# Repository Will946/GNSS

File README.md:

# ZED-F9P RTK GPS Receiver

Board for an autonomous cart that follows the edge of a lawn and sprays weed killer along the border. Goal is centimeter level positioning using RTK corrections so the cart can hold a precise line along a mapped boundary. Prototyping this board is the only part of the project built so far.

## Status

Not currently in use on the cart. Prototyping this board cost way more than expected, and the rest of the cart, drive base, sprayer, controller, was never built as a result. Right now this is just the GNSS board sitting on its own.

## Overview

The ZED-F9P decodes both L1 and L2 bands at the same time, which speeds up how fast it locks a fixed RTK solution and helps under partial sky obstruction, useful near fences, trees, or the edge of a house. With a clear view of sky and a valid RTCM3 correction stream, this board is capable of about 10 mm 3D accuracy.

Two things it needs to actually hit that accuracy:
- Clear sky view. RTK does not work well indoors or under heavy tree cover.
- A correction stream, either from a second ZED-F9P set up as a base station, or from an NTRIP correction service.

## Features

- u-blox ZED-F9P module, L1/L2 dual band, multi constellation
- Rover mode for the cart, with base station mode available if running your own fixed reference
- About 10 mm 3D accuracy with valid RTK corrections
- Update rates up to 20 Hz in high precision RTK mode
- Five simultaneous communication interfaces, see below
- U.FL antenna connector for a low profile L1/L2 active antenna
- Rechargeable backup cell that keeps module config and almanac data through power off, so warm starts are faster. Holds state for roughly two weeks unpowered
- Status LEDs for power, PPS, and fix state

## Communication Interfaces

| Interface | Description |
|---|---|
| USB-C | Enumerates as a standard COM port, carries power and full UBX/NMEA data |
| UART1 | 3.3V TTL, general purpose NMEA/UBX I/O |
| UART2 | 3.3V TTL, dedicated to RTCM3 correction data. Input on a rover, output on a base |
| I2C DDC | u-blox's I2C implementation, shares physical pins with SPI |
| SPI | Alternate to I2C on the same pins, must be explicitly selected |

Interface select jumper: I2C and SPI share pins, so only one is active at a time.
- Jumper open, default: I2C/DDC enabled, UART1 and I2C both active
- Jumper closed: SPI enabled, this disables UART1 and I2C

Set this before wiring your host MCU. An unexpected jumper state is the most common reason I2C or SPI fails to come up.

## Hardware

| Item | Detail |
|---|---|
| GNSS module | u-blox ZED-F9P |
| Antenna connector | U.FL, active antenna with bias tee power |
| Antenna requirement | L1/L2 dual band active GNSS antenna |
| Logic level | 3.3V |
| Backup power | Rechargeable cell, retains config/almanac about 2 weeks unpowered |
| Board interconnect | 0.1" breadboard compatible headers |
| Input power | 5V or 3.3V |

## Pinout

| Pin | Function | Notes |
|---|---|---|
| 5V / 3V3 | Power in | Select per your supply |
| GND | Ground | |
| TX1 / RX1 | UART1, NMEA/UBX | 3.3V TTL, general data |
| TX2 / RX2 | UART2, RTCM3 | 3.3V TTL, correction data in/out |
| SDA / SCL | I2C, DDC | Shares pins with SPI, see jumper |
| MISO / MOSI / SCK / CS | SPI | Enabled only when jumper closed |
| PPS | Pulse per second | Precision timing output |
| SAFEBOOT | Firmware recovery | Pull low during boot to enter recovery |

## Getting Started

1. Connect an active L1/L2 GNSS antenna to the U.FL connector.
2. Set the I2C/SPI select jumper to match your intended interface. Default is open, I2C.
3. Power the board from 5V or 3.3V.
4. Connect to the module with a UBX capable configuration tool such as u-center over USB or UART1 to check satellite lock and fix status.
5. Once a valid 3D fix shows up, move to RTK setup below.

## RTK Setup

As a rover on the cart:
- Feed RTCM3 correction messages into UART2, or via I2C/SPI if you'd rather.
- Once corrections are flowing and satellite geometry cooperates, fix state moves from no fix to 3D to RTK float to RTK fixed.
- Fixed RTK is what you want before trusting the position for holding a line along the lawn edge.

If running your own base station instead of NTRIP:
- Configure survey in mode with a target accuracy and minimum observation time, for example 60 seconds and 2 meters.
- Once survey in completes, the module holds a fixed reference position and starts outputting RTCM3 corrections on UART2.
- Typical RTCM3 messages to enable: 1005 for station coordinates, 1077, 1087, 1097, 1127 for per constellation observations, 1230 for GLONASS bias.

Correction delivery options:
- A radio telemetry link, LoRa or 900 MHz, between a yard mounted base and the cart
- An NTRIP client and caster over the internet for networked corrections

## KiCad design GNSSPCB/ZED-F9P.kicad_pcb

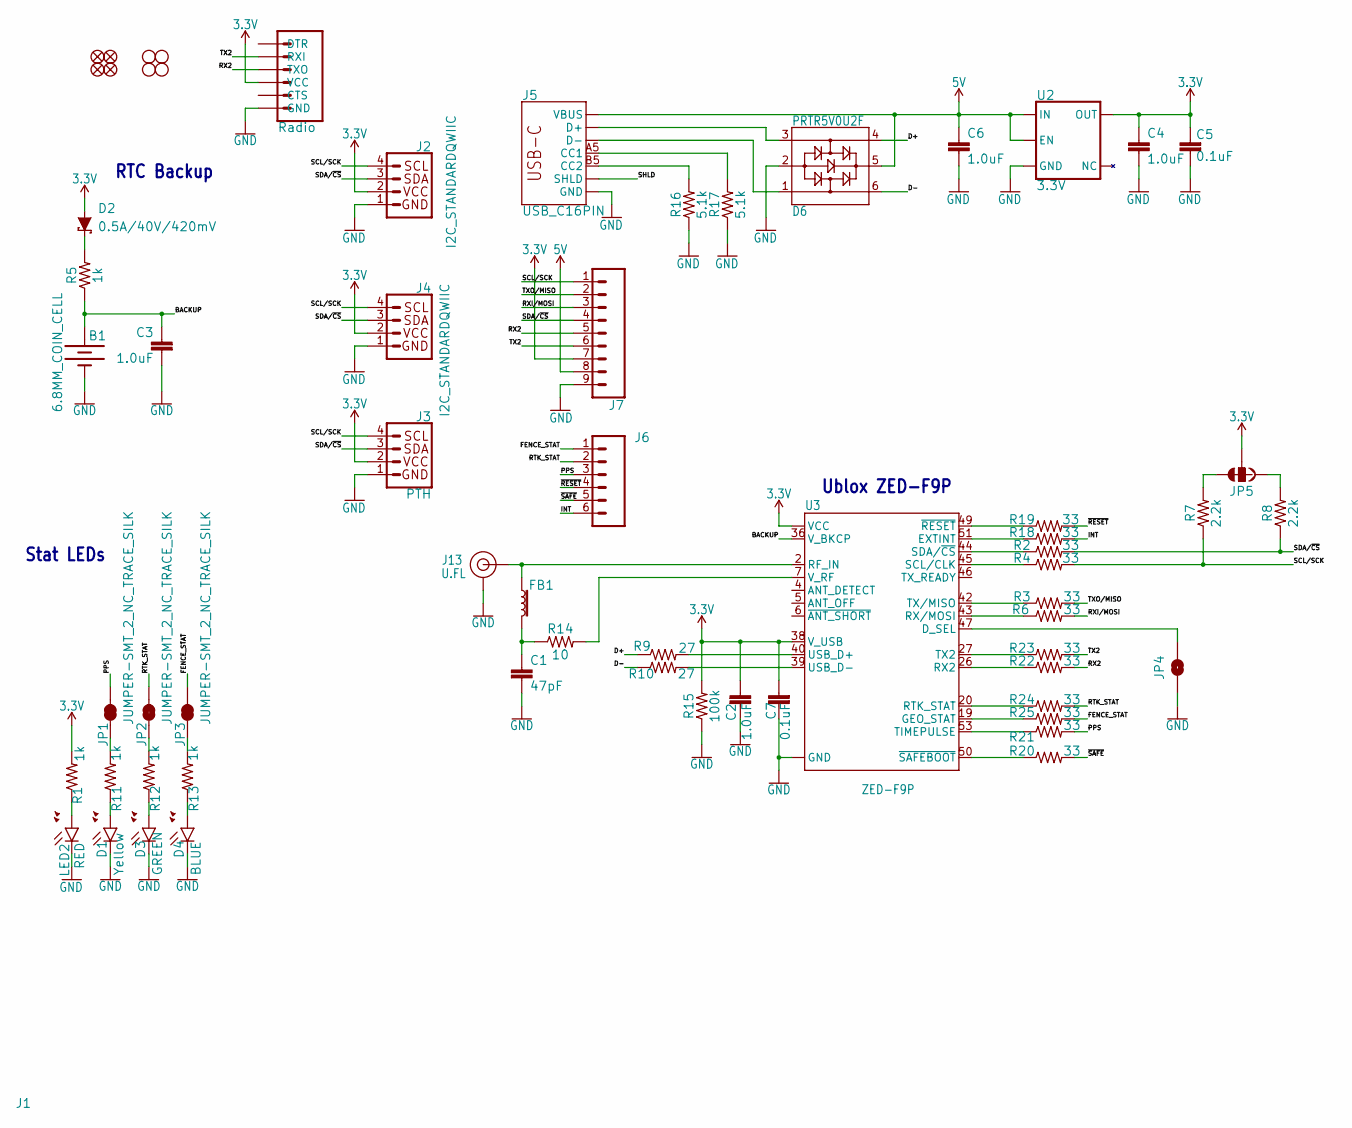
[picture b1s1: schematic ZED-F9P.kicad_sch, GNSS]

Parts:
B1: 6.8MM_COIN_CELL; BATTCON-6.8MM
C1: 47pF; 0603
C2, C3, C4, C6: 1.0uF; 0603
C5, C7: 0.1uF; 0603
D1: Yellow; LED-0603
D2: 0.5A/40V/420mV; SOD-323
D3: GREEN; LED-0603
D4: BLUE; LED-0603
D6: PRTR5V0U2F; SOT886
FB1: FERRITE_BEAD-120_OHM-0402; 0402
J1: Radio; 1X06_NO_SILK
J2, J4: I2C_STANDARDQWIIC; 1X04_1MM_RA
J3: PTH; 1X04_NO_SILK
J5: USB_C16PIN; USB-C-16P
J6: CONN_06NO_SILK_FEMALE_PTH; 1X06_NO_SILK
J7: CONN_09NO_SILK; 1X09_NO_SILK
J13: U.FL
JP1, JP2, JP3: JUMPER-SMT_2_NC_TRACE_SILK; SMT-JUMPER_2_NC_TRACE_SILK
JP4: JUMPER-SMT_2_NO_SILK; SMT-JUMPER_2_NO_SILK
JP5: JUMPER-SMT_3_2-NC_TRACE_SILK; SMT-JUMPER_3_2-NC_TRACE_SILK
JP21, JP61, JP71, JP81: FIDUCIALUFIDUCIAL; MICRO-FIDUCIAL
JP31, JP41, JP91, JP101: STAND-OFF
LED2: RED; LED-0603
R1, R5, R11, R12, R13: 1k; 0603
R2, R3, R4, R6, R18, R19, R20, R21, R22, R23, R24, R25: 33; 0603
R7, R8: 2.2k; 0603
R9, R10: 27; 0603
R14: 10; 0603
R15: 100k; 0603
R16, R17: 5.1k; 0603
U2: 3.3V; SOT23-5
U3: ZED-F9P

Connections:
3.3V: C2.1, C4.1, C5.2, C7.2, D2.A, J1.4 (VCC), J2.2, J3.2 (VCC), J4.2, J7.7, JP5.2, R1.2, R15.2, U2.5 (OUT), U3.33 (VCC), U3.34 (VCC), U3.38 (V_USB)
5V: C6.1, D6.5, J5.VBUS1 (VBUS), J5.VBUS2 (VBUS), J7.8, U2.1 (IN), U2.3 (EN)
ANT_VCC: C1.1, FB1.2, R14.1
BACKUP: B1.+, C3.1, R5.1, U3.36 (V_BKCP)
CC1: J5.A5 (CC1), R17.2
CC2: J5.B5 (CC2), R16.2
D+: D6.4, R9.1
D-: D6.6, R10.1
D_SEL: JP4.2, U3.47 (D_SEL)
FENCE_STAT: J6.1, JP3.2, R25.2
GND: B1.-, C1.2, C2.2, C3.2, C4.2, C5.1, C6.2, C7.1, D1.C, D3.C, D4.C, D6.2, J1.6 (GND), J2.1, J3.1 (GND), J4.1, J5.GND, J5.GND2 (GND), J7.9, J13.1 (GND), J13.2 (GND), JP4.1, LED2.C, R15.1, R16.1, R17.1, U2.2 (GND), U3.1 (GND), U3.3 (GND), U3.12 (GND), U3.14 (GND), U3.32 (GND), U3.37 (GND), U3.41 (GND), U3.48 (GND), U3.55 (GND), U3.56 (GND), U3.57 (GND), U3.58 (GND), U3.59 (GND), U3.60 (GND), U3.61 (GND), U3.62 (GND), U3.63 (GND), U3.64 (GND), U3.65 (GND), U3.66 (GND), U3.67 (GND), U3.68 (GND), U3.69 (GND), U3.70 (GND), U3.71 (GND), U3.72 (GND), U3.73 (GND), U3.74 (GND), U3.75 (GND), U3.76 (GND), U3.77 (GND), U3.78 (GND), U3.79 (GND), U3.80 (GND), U3.81 (GND), U3.82 (GND), U3.83 (GND), U3.84 (GND), U3.85 (GND), U3.86 (GND), U3.87 (GND), U3.88 (GND), U3.89 (GND), U3.90 (GND), U3.91 (GND), U3.92 (GND), U3.93 (GND), U3.94 (GND), U3.95 (GND), U3.96 (GND), U3.97 (GND), U3.98 (GND), U3.99 (GND), U3.100 (GND), U3.101 (GND), U3.102 (GND)
GPS_ANT1: FB1.1, J13.FEED (SIGNAL), U3.2 (RF_IN)
INT: J6.6, R18.2
unnamed: D3.A, R12.1
unnamed: D1.A, R11.1
unnamed: JP2.1, R12.2
unnamed: JP1.1, R11.2
unnamed: JP5.1, R8.2
unnamed: D2.C, R5.2
unnamed: D4.A, R13.1
unnamed: JP5.3, R7.2
unnamed: JP3.1, R13.2
unnamed: LED2.A, R1.1
unnamed: R9.2, U3.40 (USB_D+)
unnamed: R10.2, U3.39 (USB_D-)
unnamed: R14.2, U3.7 (V_RF)
unnamed: R22.1, U3.26 (RX2)
unnamed: R18.1, U3.51 (EXTINT)
unnamed: R19.1, U3.49 (~RESET)
unnamed: R21.1, U3.53 (TIMEPULSE)
unnamed: R20.1, U3.50 (~SAFEBOOT)
unnamed: R24.1, U3.20 (RTK_STAT)
unnamed: R25.1, U3.19 (GEO_STAT)
PPS: J6.3, JP1.2, R21.2
RTK_STAT: J6.2, JP2.2, R24.2
RX2: J1.3 (TXO), J7.5, R22.2
RXI/MOSI: J7.3, R6.2
RXLV: R6.1, U3.43 (RX/MOSI)
SCL/SCK: J2.4, J3.4 (SCL), J4.4, J7.1, R4.2, R7.1
SCL_LV: R4.1, U3.45 (SCL/CLK)
SDA/~CS: J2.3, J3.3 (SDA), J4.3, J7.4, R2.2, R8.1
SDA_LV: R2.1, U3.44 (SDA/~CS)
SHLD: J5.SHLD1 (SHLD), J5.SHLD2 (SHLD), J5.SHLD3 (SHLD), J5.SHLD4 (SHLD), J5.SHLD5 (SHLD), J5.SHLD6 (SHLD), J5.SHLD7 (SHLD), J5.SHLD8 (SHLD)
TX2: J1.2 (RXI), J7.6, R23.2
TX2_P: R23.1, U3.27 (TX2)
TXLV: R3.1, U3.42 (TX/MISO)
TXO/MISO: J7.2, R3.2
UNP_D+: D6.3, J5.A6 (D+), J5.B6 (D+)
UNP_D-: D6.1, J5.A7 (D-), J5.B7 (D-)
~RESET: J6.4, R19.2
~SAFE: J6.5, R20.2

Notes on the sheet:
RTC Backup
Stat LEDs
Ublox ZED-F9P

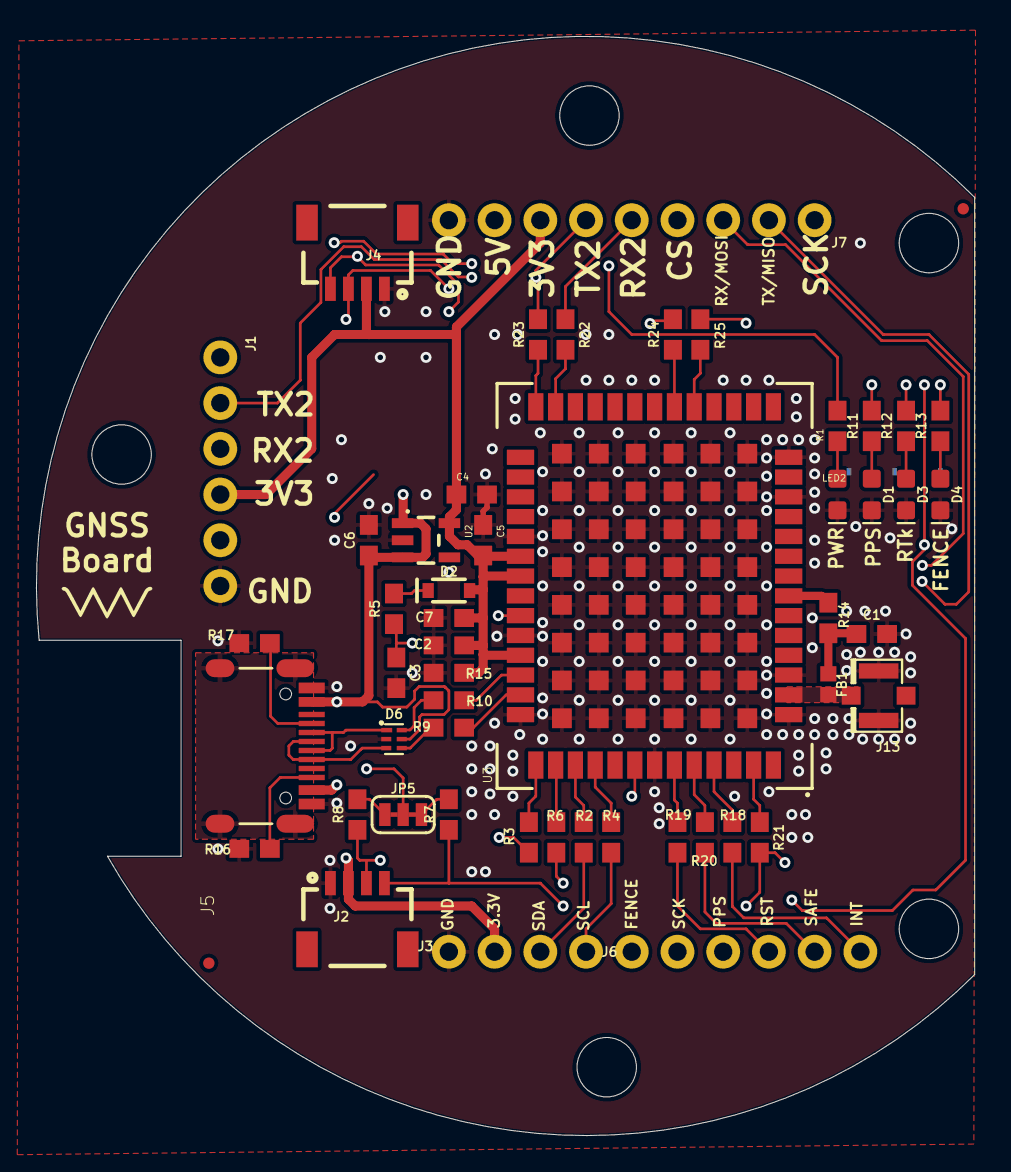
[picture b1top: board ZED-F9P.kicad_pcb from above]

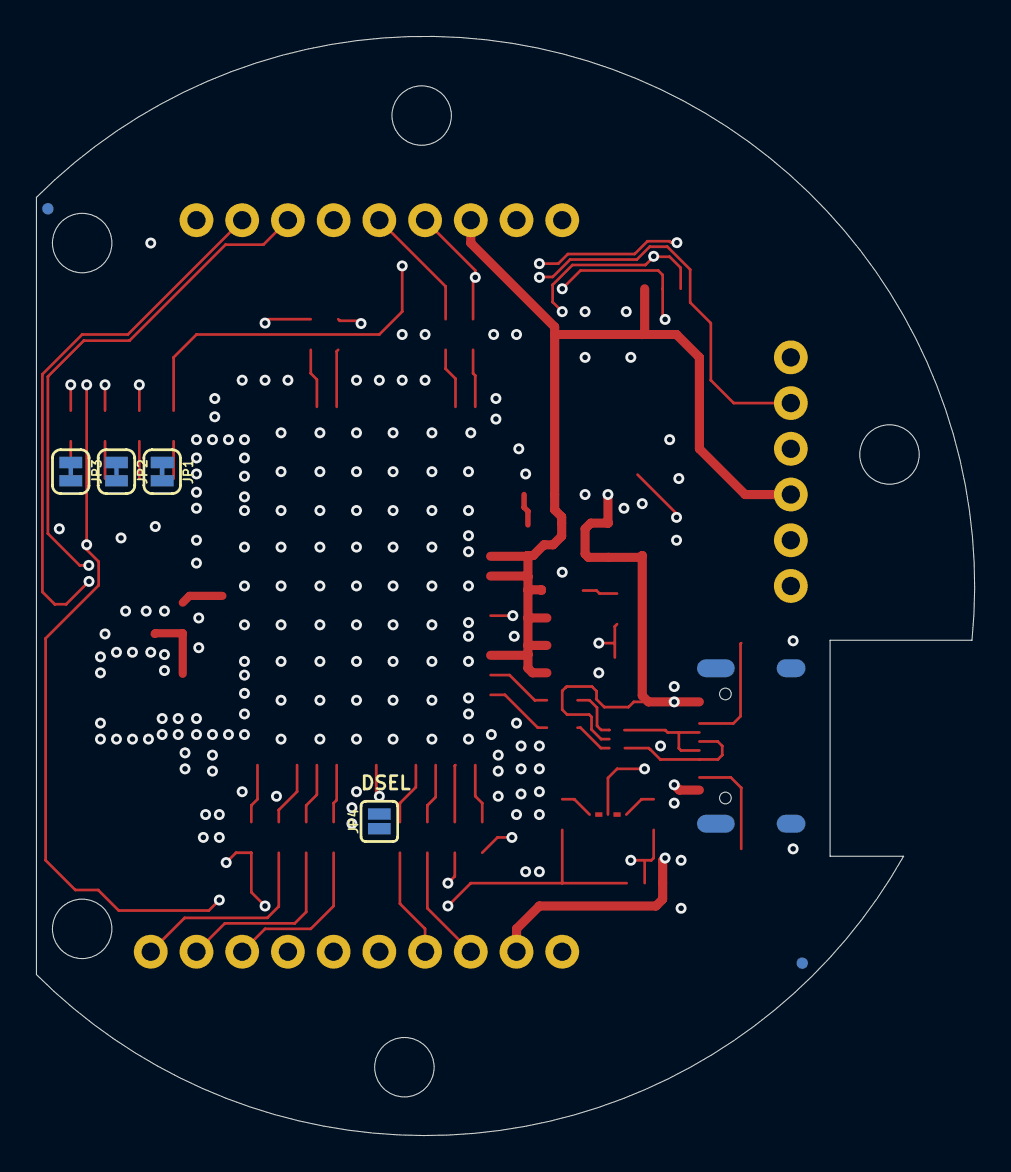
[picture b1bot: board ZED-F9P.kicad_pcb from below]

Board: 4 copper layers, 52.1 x 61.1 mm, 63 parts (6 on the bottom side), 51 nets.

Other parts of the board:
FRAME1: FRAME-LETTER; CREATIVE_COMMONS
